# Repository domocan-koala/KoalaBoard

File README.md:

# KoalaBoard

## Présentation

La KoalaBoard permet d'intégrer facilement la technologie ARM Cortex-M3 dans le système domotique [Domocan Master Édition](https://www.abcelectronique.com/bigonoff/forum/forumdisplay.php?fid=22). Ses deux connecteurs regroupent l’intégralité des entrées et sorties disponibles pour accueillir une [carte fille](https://github.com/domocan-koala/KoalaBoard_Carte-fille-template) complémentaire qui viendra spécialiser son utilisation dans votre installation. Les options disponibles se configurent grâce à des jumpers en fonction des besoins de l’utilisateur et de la carte fille qui va lui être associée.

## Caractéristiques techniques

* Alimentation 5V micro USB
* LPC1768 cadencé à 100MHz
* Connecteur JTAG 2x10 pins
* USB Slave
* Deux drivers CAN (*SN65HVD230*)
* Mémoire EEPROM (*24LC512*)
* Buzzer
* Support de pile 2032 et quartz pour le RTC
* Une led USB/INFO

## Configuration des jumpers

* **JP1** : Sélection de l'alimentation. (*Sans jumper, la carte doit être alimentée par la carte fille*)
* **JP2** : Active le Buzzer. (*La carte fille ne peut plus utiliser P1.20*)
* **JP3** : Active la LED USB/INFO. (*La carte fille ne peut plus utiliser P1.18*)
* **JP4** et **JP5** : Active la mémoire EEPROM. (*Ainsi que les deux résistances de pullup 4.7K*)
* **JP6**, **JP7**, **JP8** et **JP9** : Active l'USB Slave. (*La carte fille ne peut plus utiliser P0.29, P0.30, P1.30 et P2.09*)
* **JP10** et **JP11** : Active CAN1. (*La carte fille ne peut plus utiliser P0.00 et P0.01*)
* **JP12** et **JP13** : Active CAN2. (*La carte fille ne peut plus utiliser P0.04 et P0.05*)
* **JP14** : Active la LED POWER
* **JP15** : Active la résistance de terminaison CAN2
* **JP16** : Active la résistance de terminaison CAN1

## Historique
	
	* 23/02/18 V1.0 : Première version mise en ligne

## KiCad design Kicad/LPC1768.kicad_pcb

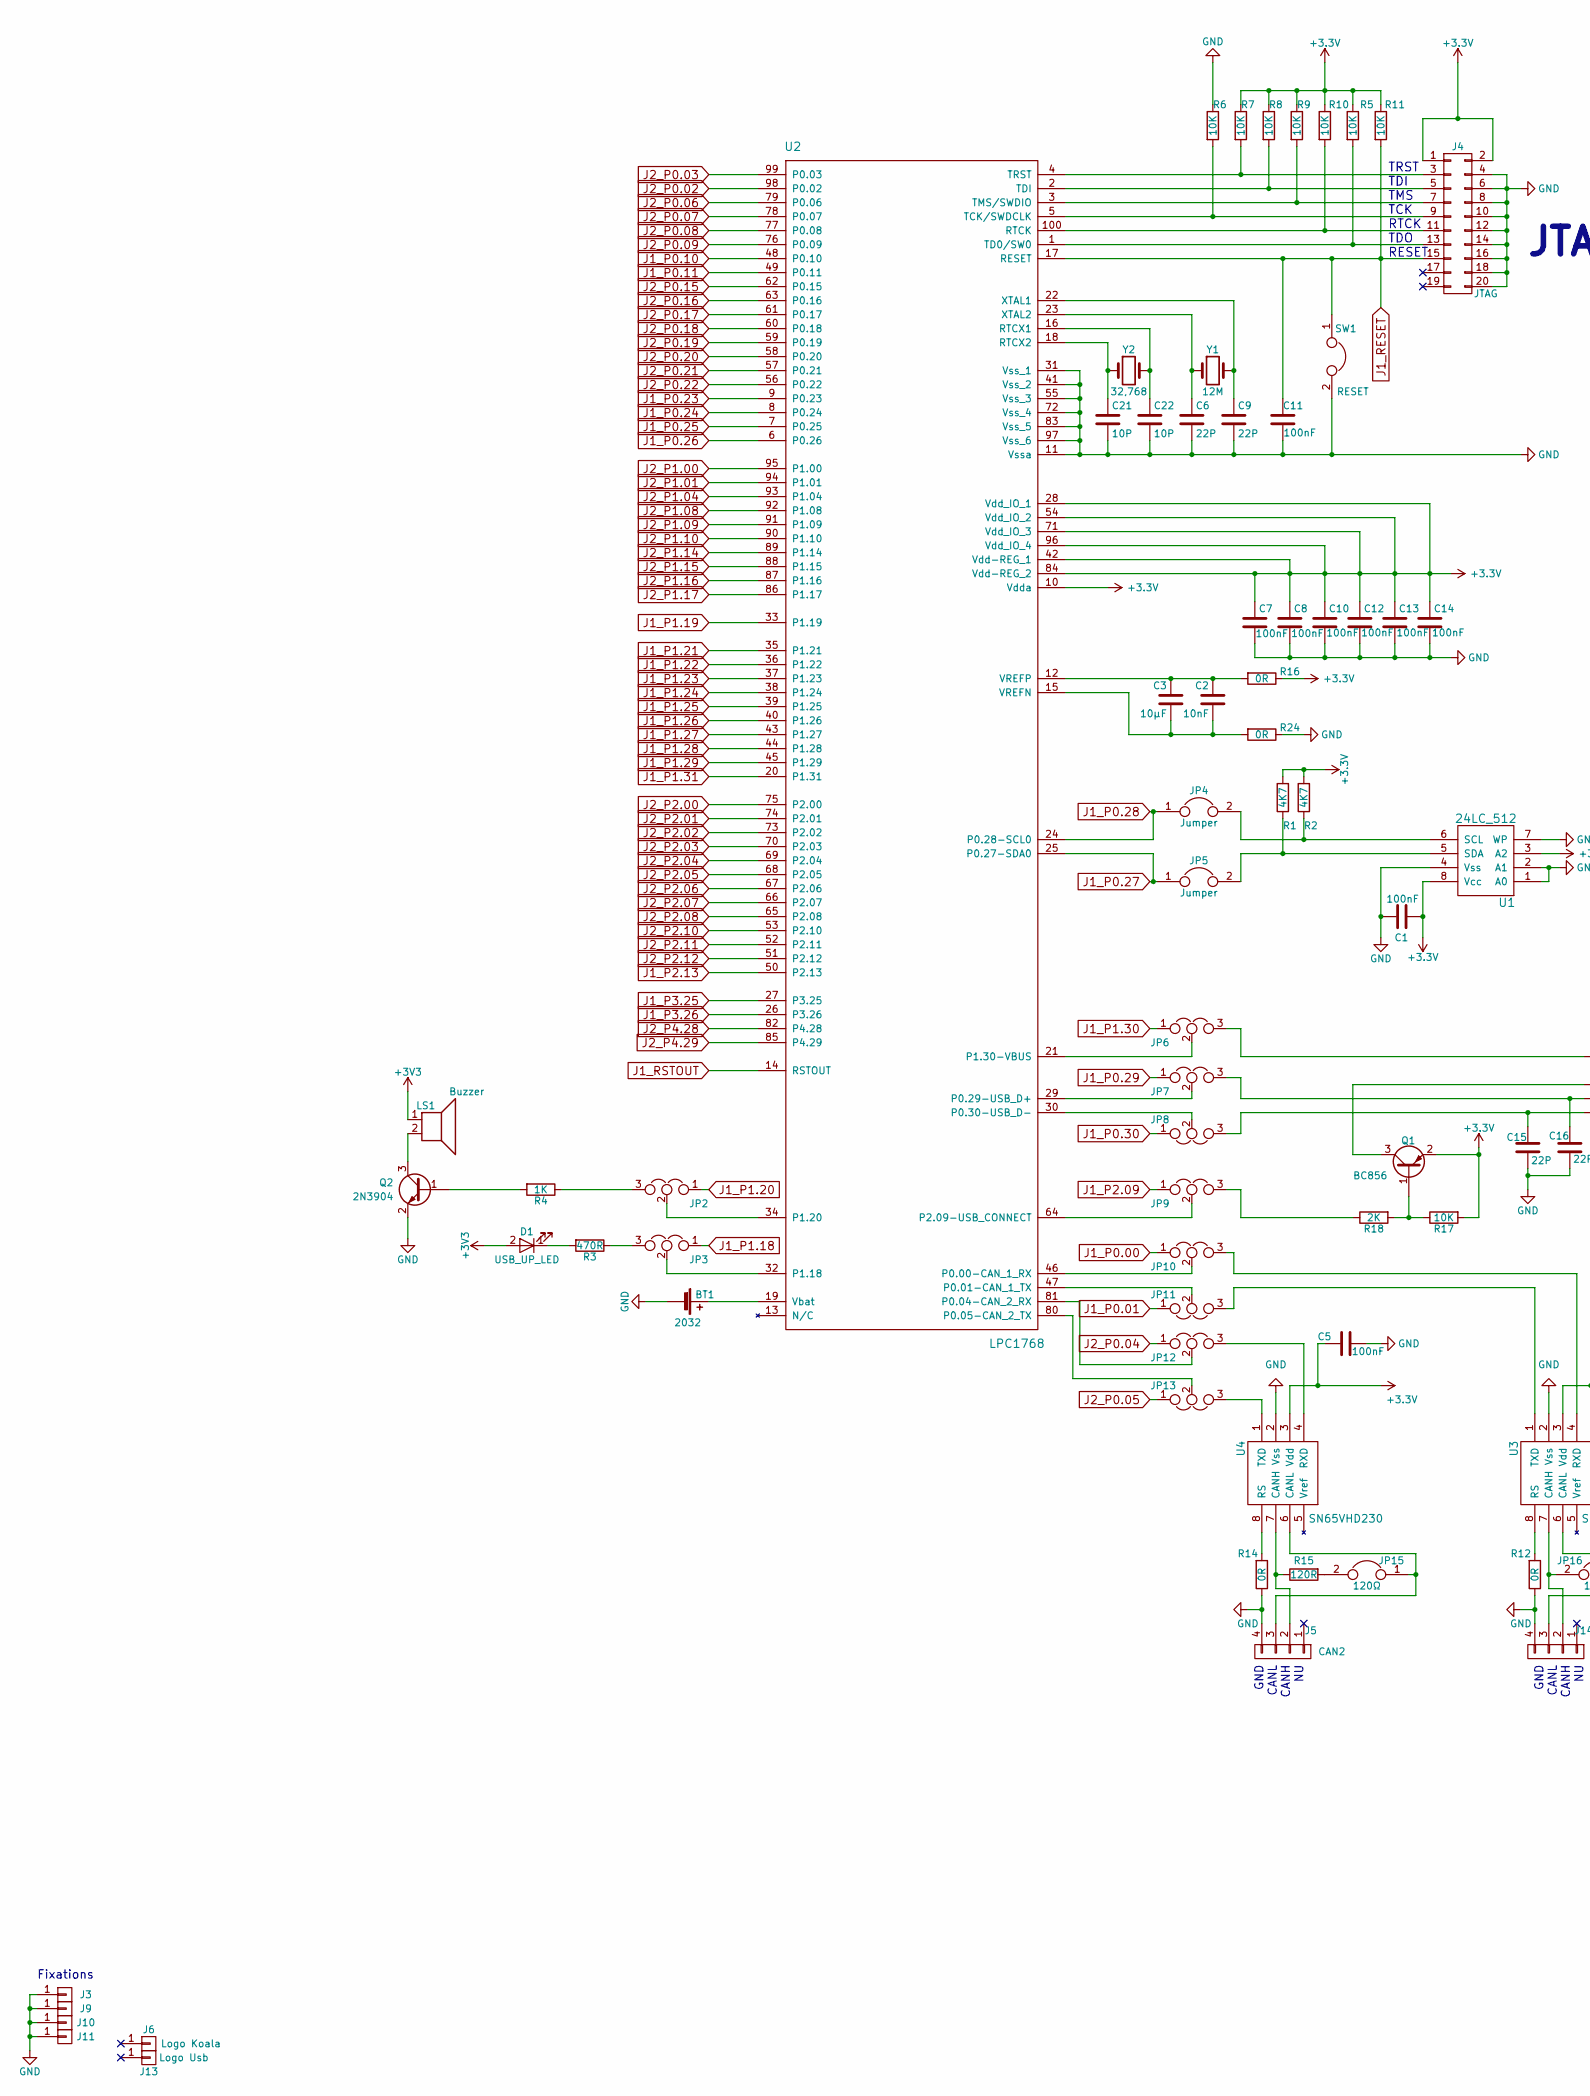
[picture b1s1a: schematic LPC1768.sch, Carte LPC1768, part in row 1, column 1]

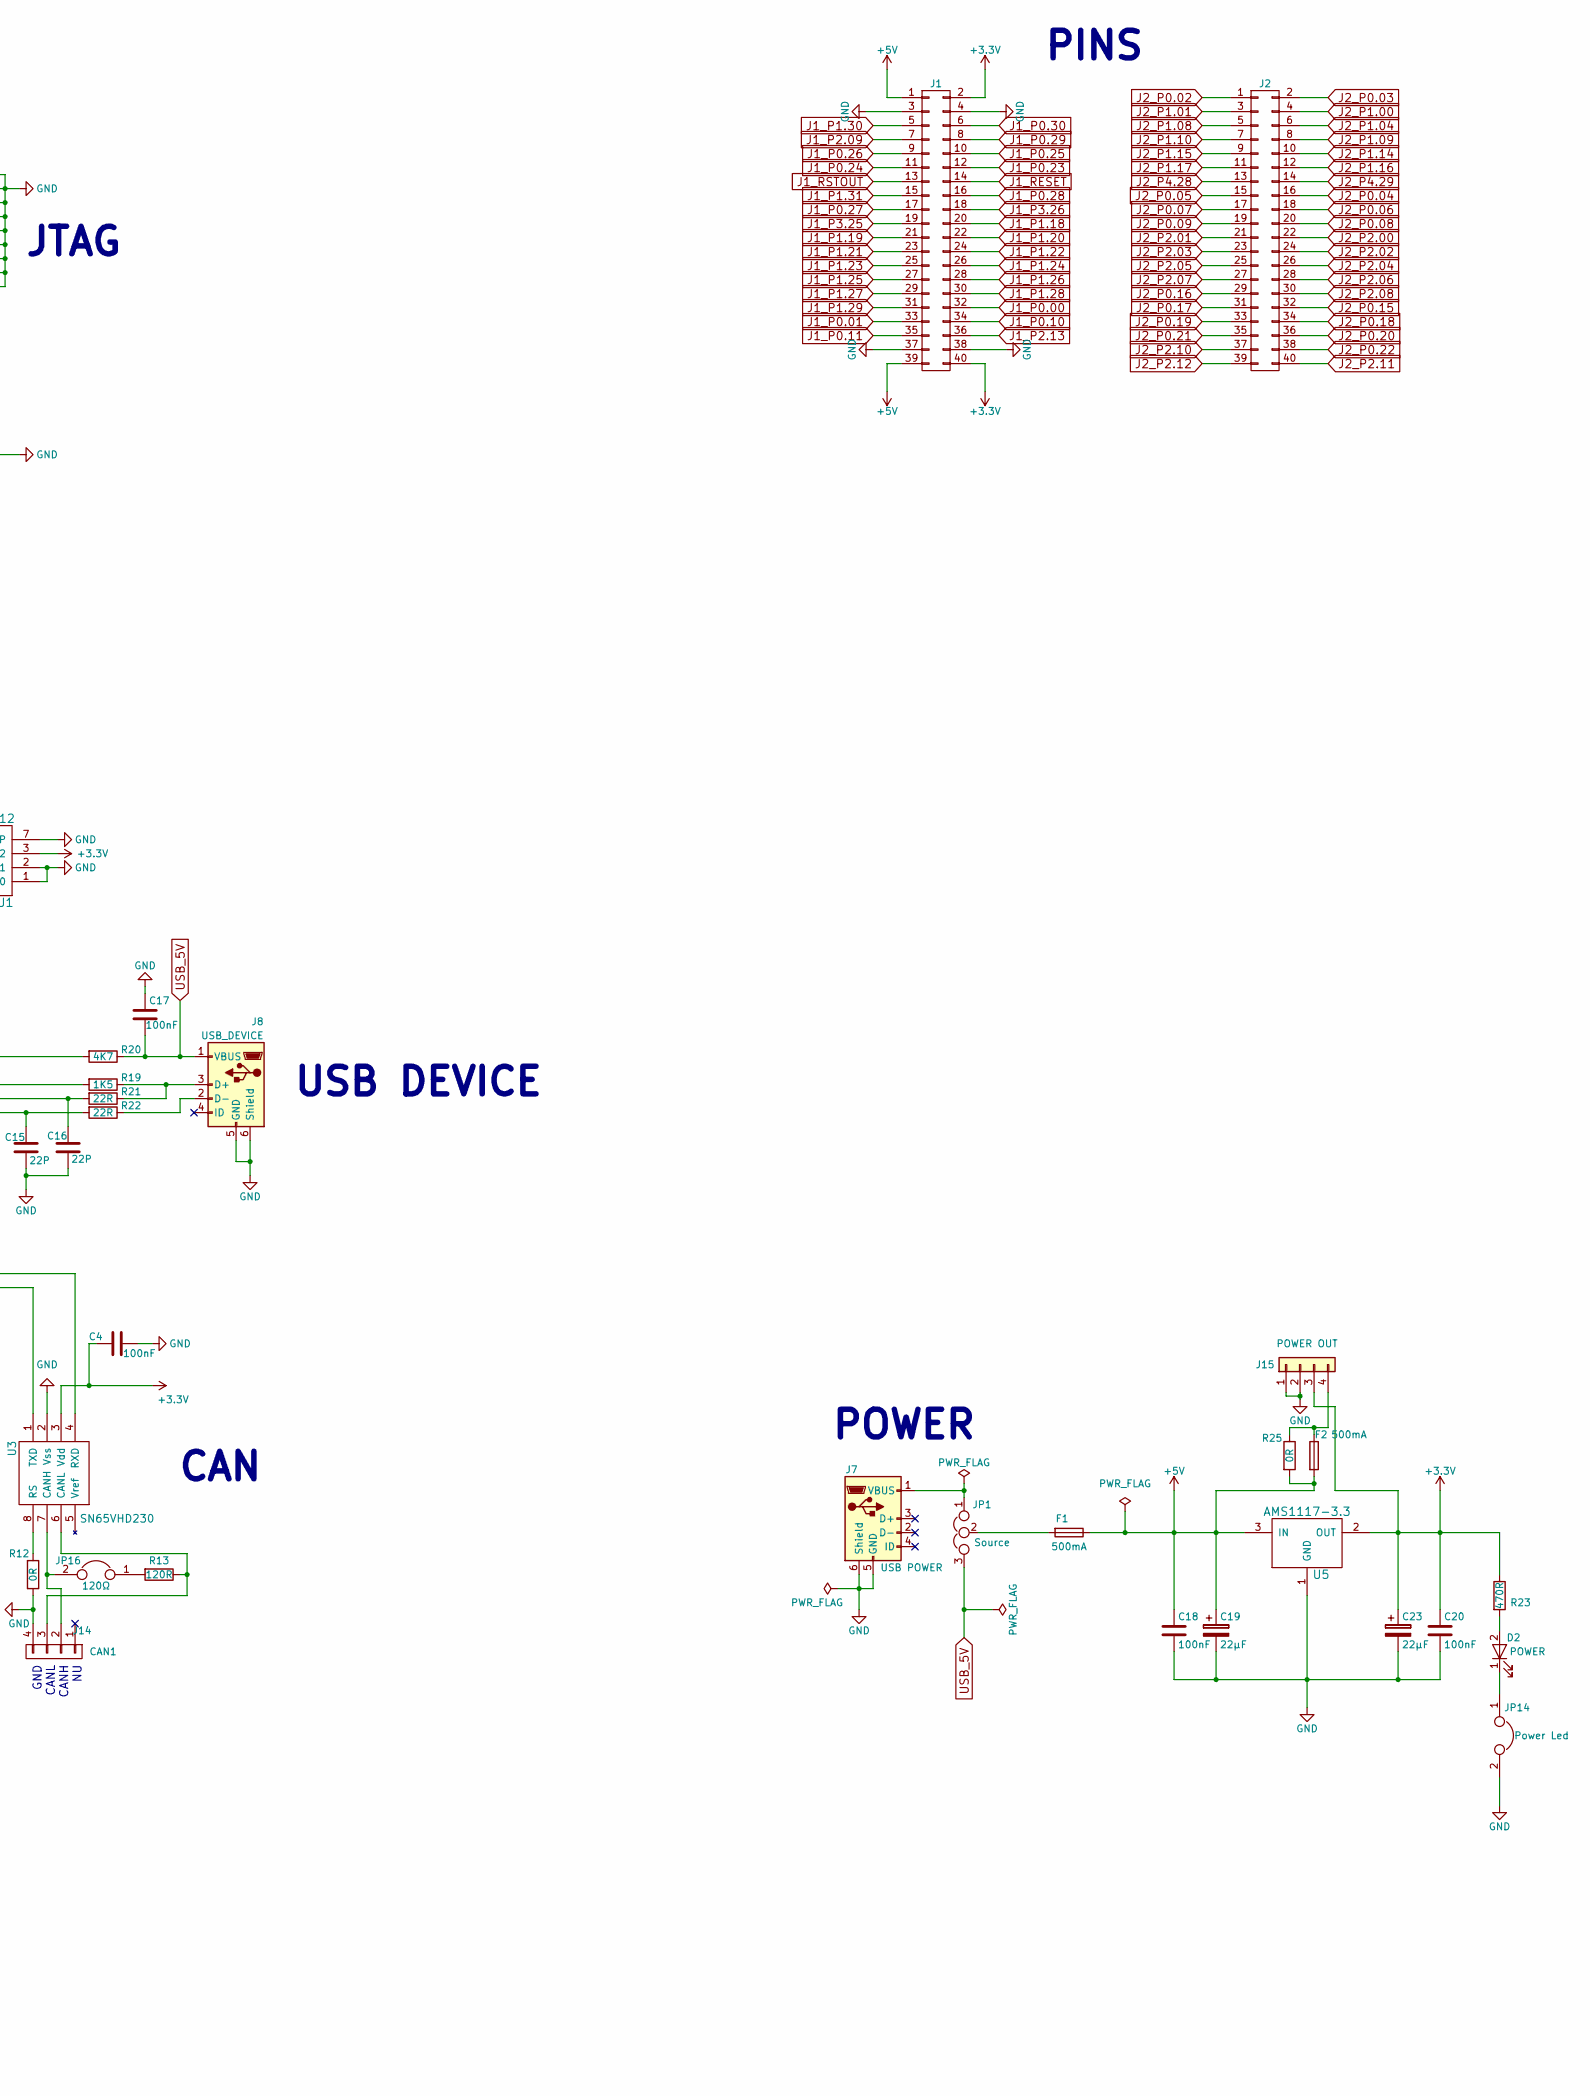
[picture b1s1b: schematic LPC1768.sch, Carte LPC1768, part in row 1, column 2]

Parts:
BT1: 2032; 2032H
C1, C4, C5, C7, C8, C10, C11, C12, C13, C14, C17, C18, C20: 100nF; C_0805_HandSoldering
C2: 10nF; C_0805_HandSoldering
C3: 10µF; C_0805_HandSoldering
C6, C9, C15, C16: 22P; C_0805_HandSoldering
C19, C23: 22µF; CP_Elec_5x5.3
C21, C22: 10P; C_0805_HandSoldering
D1: USB_UP_LED; LED_0805_HandSoldering
D2: POWER; LED_0805_HandSoldering
F1, F2: 500mA; Fuse_SMD1206_HandSoldering
J1, J2: CONN_02X20; Socket_Strip_Straight_2x20_Pitch2.54mm
J3, J9, J10, J11: CONN_01X01; MountingHole_3.5mm_Pad
J4: JTAG; JTAG_Angle_20Pins_Pitch2.54mm
J5: CAN2; Pin_Header_Angled_1x04
J6: Logo Koala; koala
J7: USB POWER; USB_Micro_B_0.65mm
J8: USB_DEVICE; USB_Micro_B_0.65mm
J13: Logo Usb; usb
J14: CAN1; Pin_Header_Angled_1x04
J15: POWER OUT; PhoenixContact_MC-G_04x3.81mm_Angled
JP1: Source; Pin_Header_Straight_1x03_Pitch2.54mm
JP2, JP3, JP9, JP10, JP11, JP12, JP13: USB_CONNECT / P2.09; Pin_Header_Straight_1x03_Pitch2.54mm
JP4, JP5: Jumper; Pin_Header_Straight_1x02_Pitch2.54mm
JP6: VBUS / P1.30; Pin_Header_Straight_1x03_Pitch2.54mm
JP7: USB_D+ / P0.29; Pin_Header_Straight_1x03_Pitch2.54mm
JP8: USB_D- / P0.30; Pin_Header_Straight_1x03_Pitch2.54mm
JP14: Power Led; Pin_Header_Straight_1x02_Pitch2.54mm
JP15, JP16: 120Ω; Pin_Header_Straight_1x02_Pitch2.54mm
LS1: Buzzer; Buzzer_12x9.5RM7.6
Q1: BC856; SOT-23_Handsoldering
Q2: 2N3904; SOT-23_Handsoldering
R1, R2, R20: 4K7; R_0805_HandSoldering
R3, R23: 470R; R_0805_HandSoldering
R4: 1K; R_0805_HandSoldering
R5, R6, R7, R8, R9, R10, R11, R17: 10K; R_0805_HandSoldering
R12, R14, R16, R24, R25: 0R; R_0805_HandSoldering
R13, R15: 120R; R_0805_HandSoldering
R18: 2K; R_0805_HandSoldering
R19: 1K5; R_0805_HandSoldering
R21, R22: 22R; R_0805_HandSoldering
SW1: RESET; SW_Tactile_SPST_Angled_PTS645Vx83-2LFS
U1: 24LC_512; SOIC-8_3.9x4.9mm_Pitch1.27mm
U2: LPC1768; LQFP-100_14x14mm_Pitch0.5mm
U3, U4: SN65VHD230; SOIC-8_3.9x4.9mm_Pitch1.27mm
U5: AMS1117-3.3; SOT-223
Y1: 12M; Crystal_SMD_HC49-SD
Y2: 32,768; Crystal_Round_d2.0mm_Vertical

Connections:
+5V: C18.1, C19.1, F1.1, F2.2, J1.1, J1.39, R25.2, U5.3 (IN)
GND: BT1.2 (-), C1.1, C4.2, C5.2, C6.2, C7.2, C8.2, C9.2, C10.2, C11.1, C12.2, C13.2, C14.2, C15.1, C16.2, C17.1, C18.2, C19.2, C20.2, C21.2, C22.2, C23.2, J1.3, J1.4, J1.37, J1.38, J3.1, J4.4, J4.6, J4.8, J4.10, J4.12, J4.14, J4.16, J4.18, J4.20, J5.4, J7.5 (GND), J7.6 (Shield), J8.5 (GND), J8.6 (Shield), J9.1, J10.1, J11.1, J14.4, J15.1, J15.2, JP14.2, Q2.2 (E), R6.1, R12.1, R14.1, R24.1, SW1.2, U1.1 (A0), U1.2 (A1), U1.4 (Vss), U1.7 (WP), U2.11 (Vssa), U2.31 (Vss_1), U2.41 (Vss_2), U2.55 (Vss_3), U2.72 (Vss_4), U2.83 (Vss_5), U2.97 (Vss_6), U3.2 (Vss), U4.2 (Vss), U5.1 (GND)
J1_P0.00: J1.32, JP10.1
J1_P0.01: J1.33, JP11.1
J1_P0.10: J1.34, U2.48 (P0.10)
J1_P0.11: J1.35, U2.49 (P0.11)
J1_P0.23: J1.12, U2.9 (P0.23)
J1_P0.24: J1.11, U2.8 (P0.24)
J1_P0.25: J1.10, U2.7 (P0.25)
J1_P0.26: J1.9, U2.6 (P0.26)
J1_P0.27: J1.17, JP5.1, U2.25 (P0.27-SDA0)
J1_P0.28: J1.16, JP4.1, U2.24 (P0.28-SCL0)
J1_P0.29: J1.8, JP7.1
J1_P0.30: J1.6, JP8.1
J1_P1.18: J1.20, JP3.1
J1_P1.19: J1.21, U2.33 (P1.19)
J1_P1.20: J1.22, JP2.1
J1_P1.21: J1.23, U2.35 (P1.21)
J1_P1.22: J1.24, U2.36 (P1.22)
J1_P1.23: J1.25, U2.37 (P1.23)
J1_P1.24: J1.26, U2.38 (P1.24)
J1_P1.25: J1.27, U2.39 (P1.25)
J1_P1.26: J1.28, U2.40 (P1.26)
J1_P1.27: J1.29, U2.43 (P1.27)
J1_P1.28: J1.30, U2.44 (P1.28)
J1_P1.29: J1.31, U2.45 (P1.29)
J1_P1.30: J1.5, JP6.1
J1_P1.31: J1.15, U2.20 (P1.31)
J1_P2.09: J1.7, JP9.1
J1_P2.13: J1.36, U2.50 (P2.13)
J1_P3.25: J1.19, U2.27 (P3.25)
J1_P3.26: J1.18, U2.26 (P3.26)
J1_RESET: C11.2, J1.14, J4.15, R11.2, SW1.1, U2.17 (RESET)
J1_RSTOUT: J1.13, U2.14 (RSTOUT)
J2_P0.02: J2.1, U2.98 (P0.02)
J2_P0.03: J2.2, U2.99 (P0.03)
J2_P0.04: J2.16, JP12.1
J2_P0.05: J2.15, JP13.1
J2_P0.06: J2.18, U2.79 (P0.06)
J2_P0.07: J2.17, U2.78 (P0.07)
J2_P0.08: J2.20, U2.77 (P0.08)
J2_P0.09: J2.19, U2.76 (P0.09)
J2_P0.15: J2.32, U2.62 (P0.15)
J2_P0.16: J2.29, U2.63 (P0.16)
J2_P0.17: J2.31, U2.61 (P0.17)
J2_P0.18: J2.34, U2.60 (P0.18)
J2_P0.19: J2.33, U2.59 (P0.19)
J2_P0.20: J2.36, U2.58 (P0.20)
J2_P0.21: J2.35, U2.57 (P0.21)
J2_P0.22: J2.38, U2.56 (P0.22)
J2_P1.00: J2.4, U2.95 (P1.00)
J2_P1.01: J2.3, U2.94 (P1.01)
J2_P1.04: J2.6, U2.93 (P1.04)
J2_P1.08: J2.5, U2.92 (P1.08)
J2_P1.09: J2.8, U2.91 (P1.09)
J2_P1.10: J2.7, U2.90 (P1.10)
J2_P1.14: J2.10, U2.89 (P1.14)
J2_P1.15: J2.9, U2.88 (P1.15)
J2_P1.16: J2.12, U2.87 (P1.16)
J2_P1.17: J2.11, U2.86 (P1.17)
J2_P2.00: J2.22, U2.75 (P2.00)
J2_P2.01: J2.21, U2.74 (P2.01)
J2_P2.02: J2.24, U2.73 (P2.02)
J2_P2.03: J2.23, U2.70 (P2.03)
J2_P2.04: J2.26, U2.69 (P2.04)
J2_P2.05: J2.25, U2.68 (P2.05)
J2_P2.06: J2.28, U2.67 (P2.06)
J2_P2.07: J2.27, U2.66 (P2.07)
J2_P2.08: J2.30, U2.65 (P2.08)
J2_P2.10: J2.37, U2.53 (P2.10)
J2_P2.11: J2.40, U2.52 (P2.11)
J2_P2.12: J2.39, U2.51 (P2.12)
J2_P4.28: J2.13, U2.82 (P4.28)
J2_P4.29: J2.14, U2.85 (P4.29)
unnamed: BT1.1 (+), U2.19 (Vbat)
unnamed: C2.1, C3.1, R16.2, U2.12 (VREFP)
unnamed: C2.2, C3.2, R24.2, U2.15 (VREFN)
unnamed: C6.1, U2.23 (XTAL2), Y1.1
unnamed: C9.1, U2.22 (XTAL1), Y1.2
unnamed: C15.2, JP8.3, R22.2
unnamed: C16.1, JP7.3, R21.2
unnamed: C21.1, U2.18 (RTCX2), Y2.1
unnamed: C22.1, U2.16 (RTCX1), Y2.2
unnamed: D1.1 (K), R3.2
unnamed: D2.1 (K), JP14.1
unnamed: D2.2 (A), R23.2
unnamed: F1.2, JP1.2
unnamed: F2.1, J15.4, R25.1
unnamed: J4.3, R7.2, U2.4 (TRST)
unnamed: J4.5, R8.2, U2.2 (TDI)
unnamed: J4.7, R9.2, U2.3 (TMS/SWDIO)
unnamed: J4.9, R6.2, U2.5 (TCK/SWDCLK)
unnamed: J4.11, R10.2, U2.100 (RTCK)
unnamed: J4.13, R5.2, U2.1 (TD0/SW0)
unnamed: J5.2, R15.1, U4.7 (CANH)
unnamed: J5.3, JP15.1, U4.6 (CANL)
unnamed: J7.1 (VBUS), JP1.1
unnamed: J8.2 (D-), R22.1
unnamed: J8.3 (D+), R19.1, R21.1
unnamed: J14.2, JP16.2, U3.7 (CANH)
unnamed: J14.3, R13.1, U3.6 (CANL)
unnamed: JP2.2, U2.34 (P1.20)
unnamed: JP2.3, R4.1
unnamed: JP3.2, U2.32 (P1.18)
unnamed: JP3.3, R3.1
unnamed: JP4.2, R2.1, U1.6 (SCL)
unnamed: JP5.2, R1.1, U1.5 (SDA)
unnamed: JP6.2, U2.21 (P1.30-VBUS)
unnamed: JP6.3, R20.2
unnamed: JP7.2, U2.29 (P0.29-USB_D+)
unnamed: JP8.2, U2.30 (P0.30-USB_D-)
unnamed: JP9.2, U2.64 (P2.09-USB_CONNECT)
unnamed: JP9.3, R18.1
unnamed: JP10.2, U2.46 (P0.00-CAN_1_RX)
unnamed: JP10.3, U3.4 (RXD)
unnamed: JP11.2, U2.47 (P0.01-CAN_1_TX)
unnamed: JP11.3, U3.1 (TXD)
unnamed: JP12.2, U2.81 (P0.04-CAN_2_RX)
unnamed: JP12.3, U4.4 (RXD)
unnamed: JP13.2, U2.80 (P0.05-CAN_2_TX)
unnamed: JP13.3, U4.1 (TXD)
unnamed: JP15.2, R15.2
unnamed: JP16.1, R13.2
unnamed: LS1.2, Q2.3 (C)
unnamed: Q1.1 (B), R17.1, R18.2
unnamed: Q1.3 (C), R19.2
unnamed: Q2.1 (B), R4.2
unnamed: R12.2, U3.8 (RS)
unnamed: R14.2, U4.8 (RS)
USB_5V: C17.2, J8.1 (VBUS), JP1.3, R20.1

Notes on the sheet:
USB DEVICE
POWER
TRST TDI TMS TCK RTCK TDO RESET
GND CANL CANH NU
PINS
JTAG
CAN
Fixations

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
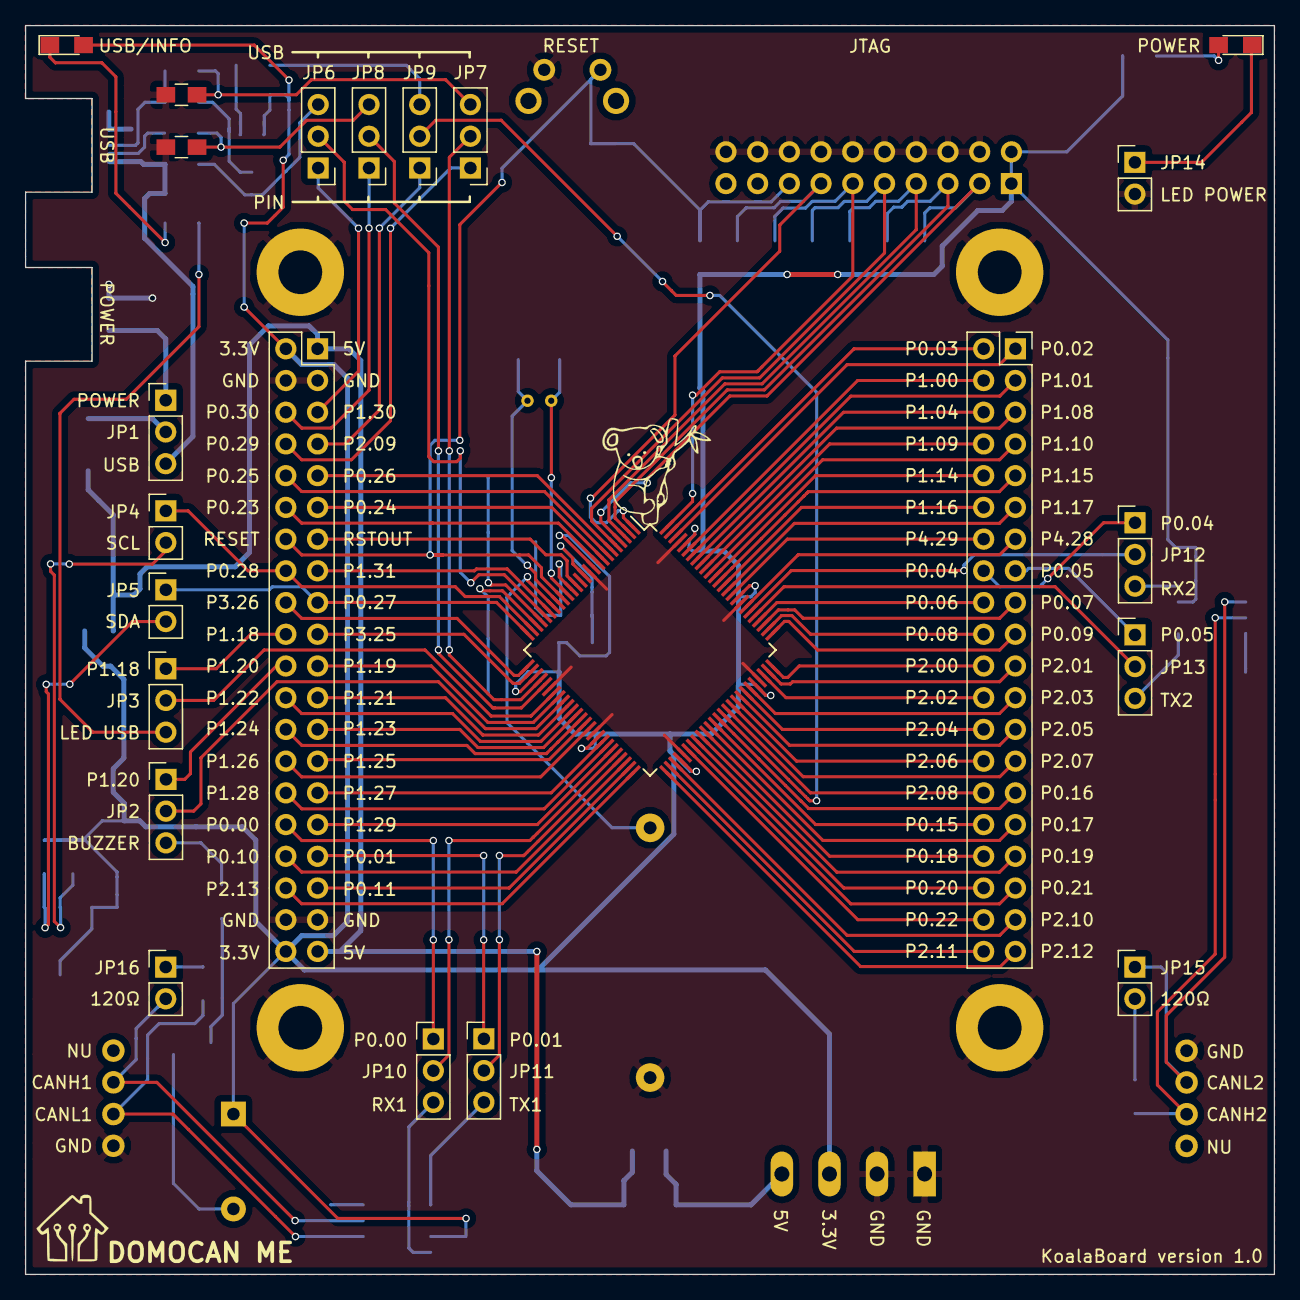
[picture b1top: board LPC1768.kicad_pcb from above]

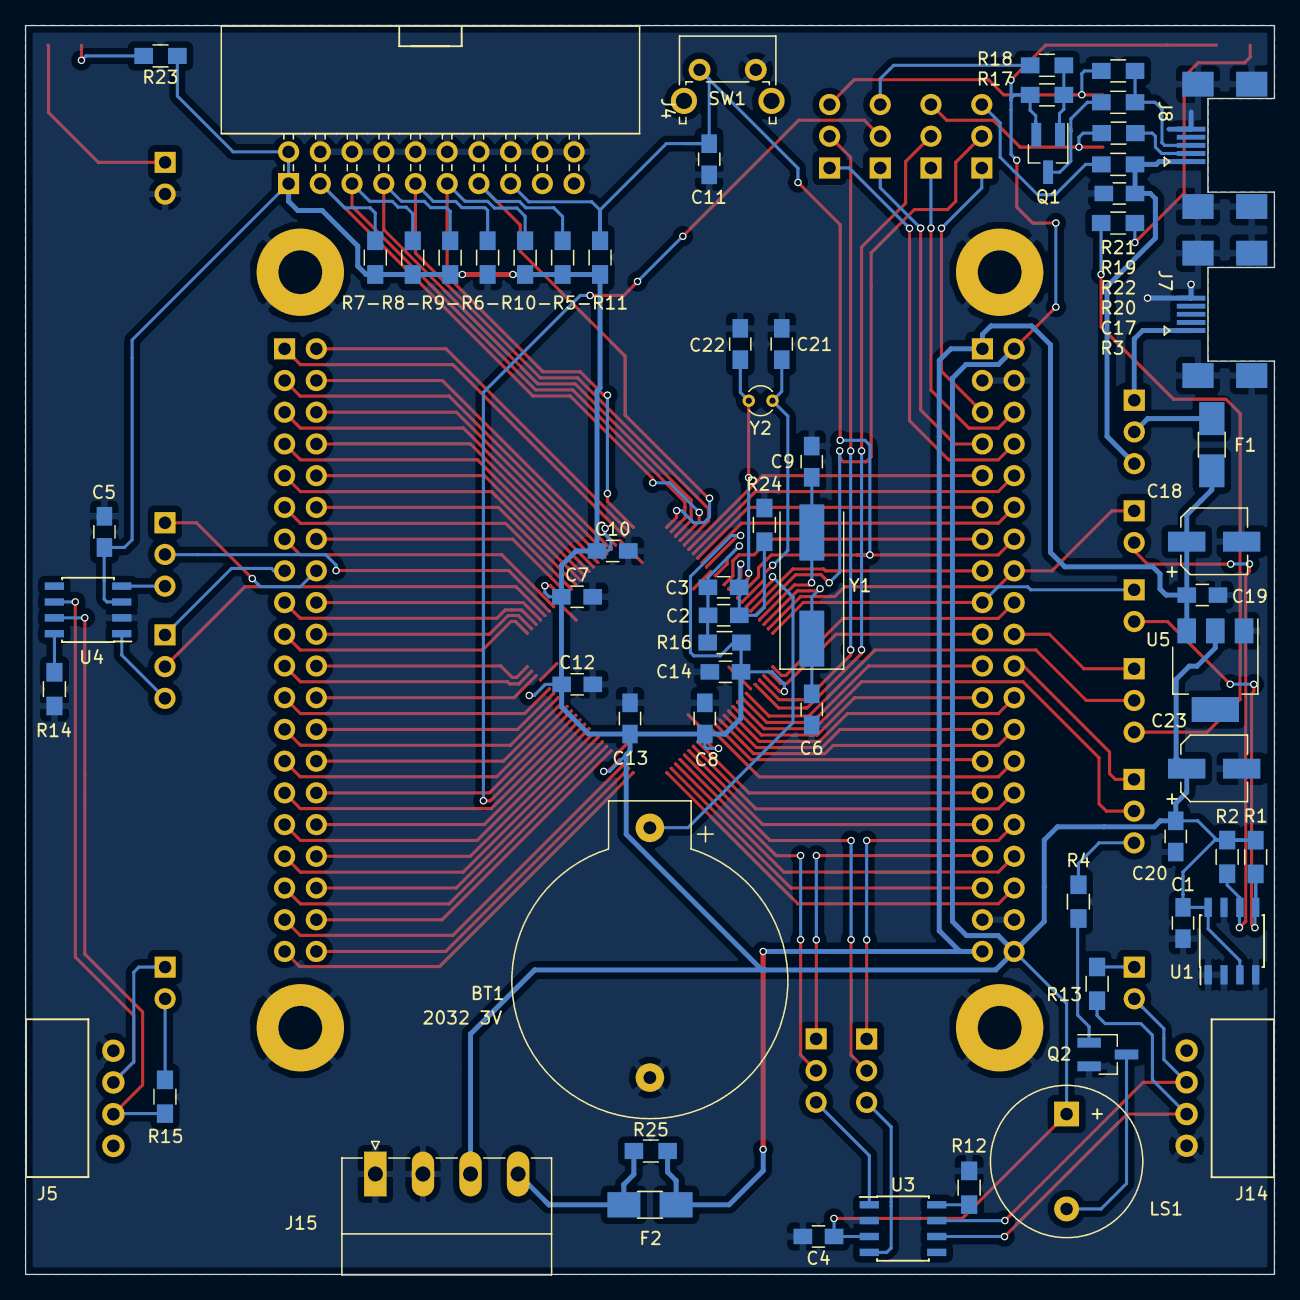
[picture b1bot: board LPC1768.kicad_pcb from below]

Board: 2 copper layers, 100.0 x 100.0 mm, 94 parts (65 on the bottom side), 131 nets.

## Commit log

2018-02-23 Première mise en ligne
    Carte mère KoalaBoard pour Domocan
2018-02-26 Documentation
    Mise à jour de la documentation
2018-02-27 Correction vue 3D
